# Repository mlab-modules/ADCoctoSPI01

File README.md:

# ADCoctoSPI01 - Octal Input High-Speed ADC Module

The ADCoctoSPI01 is an eight-channel, high-speed analog-to-digital conversion module designed for signal acquisition in imaging and similar high-speed applications. It integrates a Texas Instruments AFE5801 analog front-end (AFE), which combines eight variable-gain amplifiers (VGAs) and eight 12-bit ADCs with a sampling rate up to 65 MSPS. Data output is serialized through an LVDS interface.

This module is ideally used in combination with the [MPPB01 baseboard for Parallella](https://www.mlab.cz/module/MPPB01/), which features a compatible miniSAS connector, allowing for direct integration and high-speed data transfer.

## Features

* **8 differential analog input channels**
* **Integrated AFE5801 from Texas Instruments**
  * 8x VGAs with -5 dB to 31 dB gain range
  * 8x 12-bit ADCs, up to 65 MSPS sampling rate
  * Integrated anti-aliasing filter (7.5 / 10 / 14 MHz selectable)
  * Serial LVDS output
  * SPI control interface
* **MiniSAS (SFF-8087) connector for LVDS data output**
* **Separate SPI interface for configuration and diagnostics**
* **On-board linear regulators for 1.8V and 3.3V supplies**
* **Operating voltage: 3.6 V to 5.4 V**
* **Operating temperature: -20 °C to +40 °C**

## Technical Specifications

| Parameter                       | Value             | Description                          |
| ------------------------------- | ----------------- | ------------------------------------ |
| ADC Resolution                  | 12 bits           | Per channel                          |
| Number of Channels              | 8                 | Differential                         |
| Max Sampling Rate               | 65 MSPS           | Per channel                          |
| Input Voltage Swing             | 2 Vpp             | Differential, max linear input range |
| VGA Gain Range                  | -5 dB to +31 dB   | Step size: 0.125/1 dB                |
| Input Referred Noise            | 5.5 nV/√Hz        | At VGA gain = 31 dB                  |
| Signal-to-Noise Ratio (SNR)     | ~65 dBFS          | Typical at 65 MSPS, -1 dBFS input    |
| Total Harmonic Distortion (THD) | -65 dBFS          | At 5 MHz input, max gain             |
| Signal-to-Noise and Distortion Ratio (SINAD) | ~68 dB            |                                      |
| Antialias Filter Cutoff         | 7.5 / 10 / 14 MHz | Programmable                         |
| Common-Mode Input Voltage (VCM) | 1.6 V             | Recommended bias for AC coupling     |
| Input Capacitance               | 2 pF              | Differential input                   |
| Input Resistance                | 5 kΩ              | To internal bias                     |

## Connectors

* **J1-J4**: Differential analog inputs (IN1P/M to IN8P/M) (SATA connectors)
* **J10A**: MiniSAS connector for serialized LVDS data (D1-D8, FCLK, DCLK)
* **J8**: SPI control interface (SCLK, SDATA, SDOUT, SEN, RESET, SYNC)
* **J11**: Power input (+5V, GND)

## Power Supply

* Requires a single 5V power supply.
* Onboard regulators generate 3.3V and 1.8V for AFE operation.

## AFE5801 Configuration Highlights

* **Gain Control**: SPI-controlled VGA gain, from -5 dB to 31 dB in 0.125 dB or 1 dB steps
* **Clamping and Filtering**: Optional signal clamping and integrated third-order low-pass filter
* **Sampling Clock**: Differential clock input (LVDS/PECL supported)
* **LVDS Output**: Serialized outputs for each channel (D1-D8), frame clock (FCLK), and data clock (DCLK)

## Typical Applications

* Medical ultrasound systems
* Non-destructive testing
* High-speed data acquisition
* Multichannel signal digitization in SDR receivers

## References

* [AFE5801 Datasheet](https://www.ti.com/product/AFE5801)
* Other compatible AFEs: AFE5805, AFE5809 (with differing performance and power specs)

## Notes

* Only the AFE5801 is populated by default; board supports footprint-compatible variants (AFE5803, AFE5804 etc.).
* For optimal performance, ensure proper analog signal termination and impedance matching on all differential inputs.
* Follow ESD precautions during handling.

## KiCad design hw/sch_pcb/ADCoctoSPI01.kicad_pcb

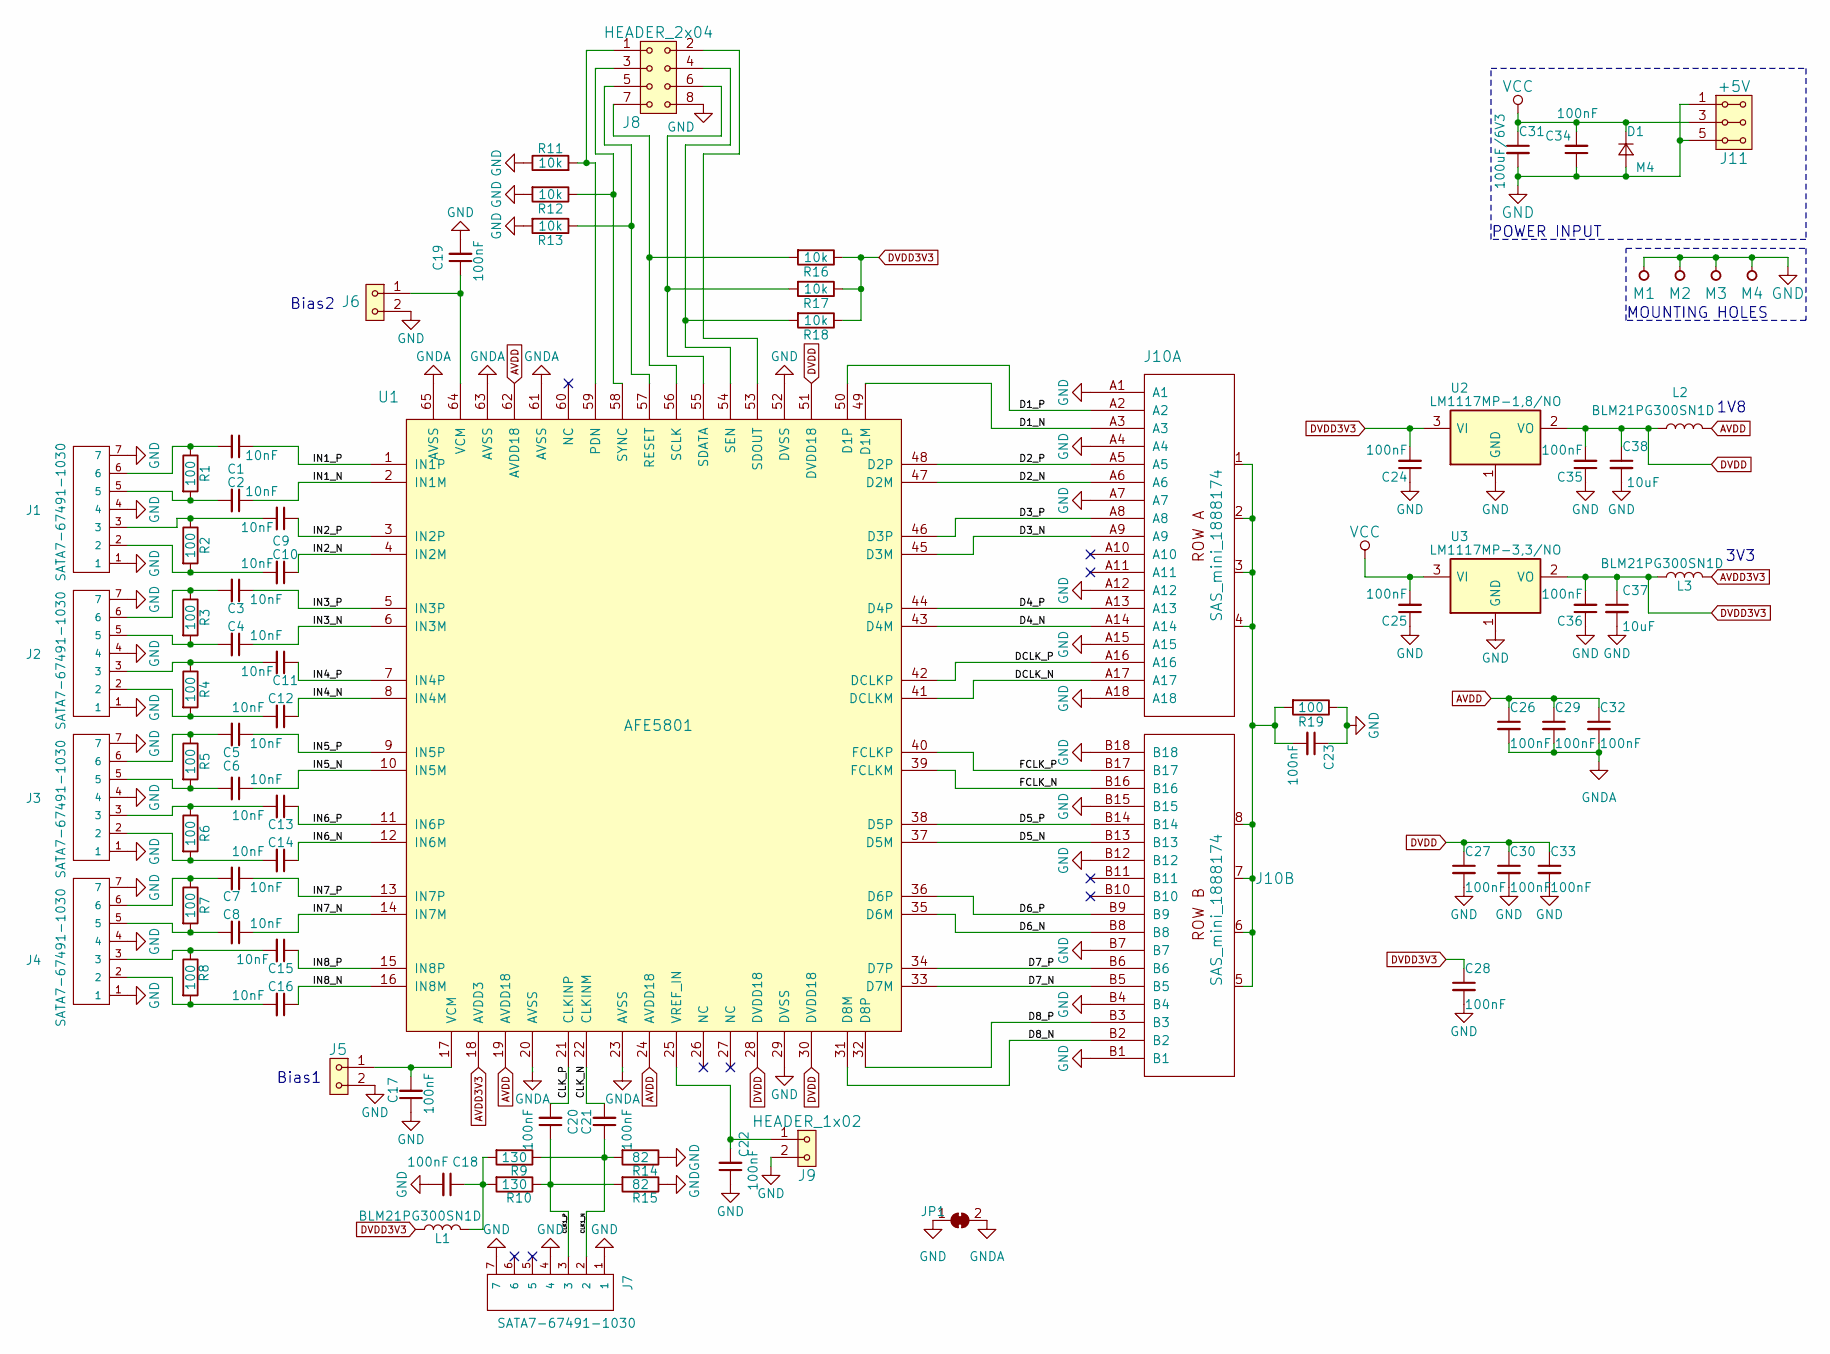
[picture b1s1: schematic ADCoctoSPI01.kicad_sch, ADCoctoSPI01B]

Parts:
C1, C2, C3, C4, C5, C6, C7, C8, C9, C10, C11, C12, C13, C14, C15, C16: 10nF; C_0603_1608Metric
C17, C18, C19, C20, C21, C22, C23, C24, C25, C26, C27, C28, C29, C30, C32, C33, C34, C35, C36: 100nF; C_0603_1608Metric
C31: 100uF/6V3; C_1210_3225Metric_Pad1.33x2.70mm_HandSolder
C37, C38: 10uF; C_0805_2012Metric
D1: M4; D_SMA
J1, J2, J3, J4, J7: SATA7-67491-1030; SATA-7_THT_VERT_2
J5, J6, J9: HEADER_1x02; Straight_1x02
J8: HEADER_2x04; Straight_2x04
J10: SAS_mini_1888174; SAS-mini_TEConnectivity_1888174_Vertical
J11: +5V; Straight_2x03
JP1: SolderJumper_2_Bridged; NetTie-2_SMD_Pad0.5mm
L1, L2, L3: BLM21PG300SN1D; L_0805_2012Metric_Pad1.15x1.40mm_HandSolder
M1, M2, M3, M4: HOLE; MountingHole_3mm
R1, R2, R3, R4, R5, R6, R7, R8, R19: 100; R_0603_1608Metric
R9, R10: 130; R_0603_1608Metric
R11, R12, R13, R16, R17, R18: 10k; R_0603_1608Metric
R14, R15: 82; R_0603_1608Metric
U1: AFE5801; VQFN-64_9.15x9.15mm_EP_7.5x7.5mm
U2: LM1117MP-1,8/NO; SOT-223-3_TabPin2
U3: LM1117MP-3,3/NO; SOT-223-3_TabPin2

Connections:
/CLK1_N: C21.1, J7.2, R9.1, R14.2
/CLK1_P: C20.1, J7.3, R10.1, R15.2
/CLK_N: C21.2, U1.22 (CLKINM)
/CLK_P: C20.2, U1.21 (CLKINP)
/D1_N: J10.A3, U1.49 (D1M)
/D1_P: J10.A2, U1.50 (D1P)
/D2_N: J10.A6, U1.47 (D2M)
/D2_P: J10.A5, U1.48 (D2P)
/D3_N: J10.A9, U1.45 (D3M)
/D3_P: J10.A8, U1.46 (D3P)
/D4_N: J10.A14, U1.43 (D4M)
/D4_P: J10.A13, U1.44 (D4P)
/D5_N: J10.B13, U1.37 (D5M)
/D5_P: J10.B14, U1.38 (D5P)
/D6_N: J10.B8, U1.35 (D6M)
/D6_P: J10.B9, U1.36 (D6P)
/D7_N: J10.B5, U1.33 (D7M)
/D7_P: J10.B6, U1.34 (D7P)
/D8_N: J10.B2, U1.31 (D8M)
/D8_P: J10.B3, U1.32 (D8P)
/DCLK_N: J10.A17, U1.41 (DCLKM)
/DCLK_P: J10.A16, U1.42 (DCLKP)
/FCLK_N: J10.B16, U1.39 (FCLKM)
/FCLK_P: J10.B17, U1.40 (FCLKP)
/IN1_N: C2.1, U1.2 (IN1M)
/IN1_P: C1.1, U1.1 (IN1P)
/IN2_N: C10.1, U1.4 (IN2M)
/IN2_P: C9.1, U1.3 (IN2P)
/IN3_N: C4.1, U1.6 (IN3M)
/IN3_P: C3.1, U1.5 (IN3P)
/IN4_N: C12.1, U1.8 (IN4M)
/IN4_P: C11.1, U1.7 (IN4P)
/IN5_N: C6.1, U1.10 (IN5M)
/IN5_P: C5.1, U1.9 (IN5P)
/IN6_N: C14.1, U1.12 (IN6M)
/IN6_P: C13.1, U1.11 (IN6P)
/IN7_N: C8.1, U1.14 (IN7M)
/IN7_P: C7.1, U1.13 (IN7P)
/IN8_N: C16.1, U1.16 (IN8M)
/IN8_P: C15.1, U1.15 (IN8P)
AVDD: C26.1, C29.1, C32.1, L2.2, U1.19 (AVDD18), U1.24 (AVDD18), U1.62 (AVDD18)
AVDD3V3: L3.2, U1.18 (AVDD3)
DVDD: C27.1, C30.1, C33.1, C35.2, C38.1, L2.1, U1.28 (DVDD18), U1.30 (DVDD18), U1.51 (DVDD18), U2.2 (VO)
DVDD3V3: C24.2, C28.1, C36.2, C37.1, L1.1, L3.1, R16.1, R17.1, R18.1, U2.3 (VI), U3.2 (VO)
GND: C17.1, C18.2, C19.2, C22.1, C23.1, C24.1, C25.1, C27.2, C28.2, C30.2, C31.2, C33.2, C34.1, C35.1, C36.1, C37.2, C38.2, D1.2 (A), J1.1, J1.4, J1.7, J2.1, J2.4, J2.7, J3.1, J3.4, J3.7, J4.1, J4.4, J4.7, J5.2, J6.2, J7.1, J7.4, J7.7, J8.8, J9.2, J10.A1, J10.A4, J10.A7, J10.A12, J10.A15, J10.A18, J10.B1, J10.B4, J10.B7, J10.B12, J10.B15, J10.B18, J11.1, J11.2, J11.5, J11.6, JP1.1 (A), M1.1, M2.1, M3.1, M4.1, R11.1, R12.2, R13.2, R14.1, R15.1, R19.1, U1.29 (DVSS), U1.52 (DVSS), U2.1 (GND), U3.1 (GND)
GNDA: C26.2, C29.2, C32.2, JP1.2 (B), U1.20 (AVSS), U1.23 (AVSS), U1.61 (AVSS), U1.63 (AVSS), U1.65 (AVSS)
unnamed: C1.2, J1.6, R1.1
unnamed: C2.2, J1.5, R1.2
unnamed: C3.2, J2.6, R3.1
unnamed: C4.2, J2.5, R3.2
unnamed: C5.2, J3.6, R5.1
unnamed: C6.2, J3.5, R5.2
unnamed: C7.2, J4.6, R7.1
unnamed: C8.2, J4.5, R7.2
unnamed: C9.2, J1.3, R2.1
unnamed: C10.2, J1.2, R2.2
unnamed: C11.2, J2.3, R4.1
unnamed: C12.2, J2.2, R4.2
unnamed: C13.2, J3.3, R6.1
unnamed: C14.2, J3.2, R6.2
unnamed: C15.2, J4.3, R8.1
unnamed: C16.2, J4.2, R8.2
unnamed: C17.2, J5.1, U1.17 (VCM)
unnamed: C18.1, L1.2, R9.2, R10.2
unnamed: C19.1, J6.1, U1.64 (VCM)
unnamed: C23.2, J10.1, J10.2, J10.3, J10.4, J10.5, J10.6, J10.7, J10.8, R19.2
unnamed: J8.1, R11.2, U1.59 (PDN)
unnamed: J8.5, R13.1, U1.57 (RESET)
unnamed: J8.7, R16.2, U1.56 (SCLK)
unnamed: J8.6, R17.2, U1.55 (SDATA)
unnamed: J8.2, U1.53 (SDOUT)
unnamed: J8.4, R18.2, U1.54 (SEN)
unnamed: J8.3, R12.1, U1.58 (SYNC)
unnamed: C22.2, J9.1, U1.25 (VREF_IN)
VCC: C25.2, C31.1, C34.2, D1.1 (K), J11.3, J11.4, U3.3 (VI)

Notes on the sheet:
Bias1
Bias2
POWER INPUT
MOUNTING HOLES
1V8
3V3

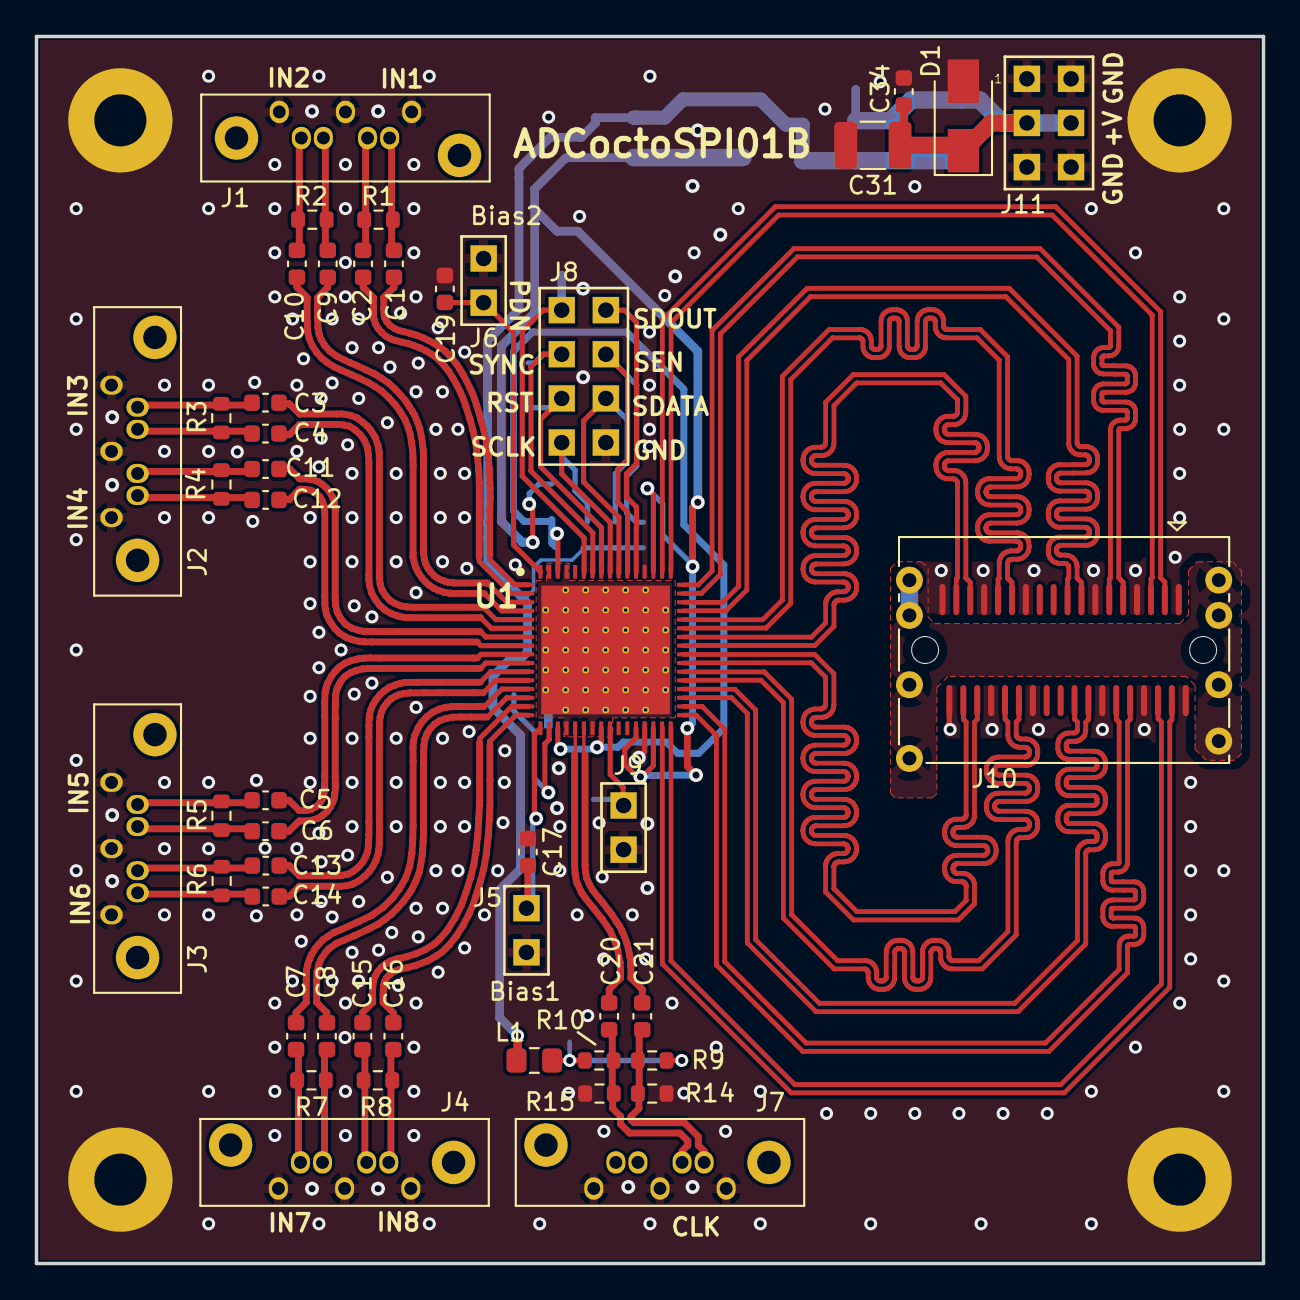
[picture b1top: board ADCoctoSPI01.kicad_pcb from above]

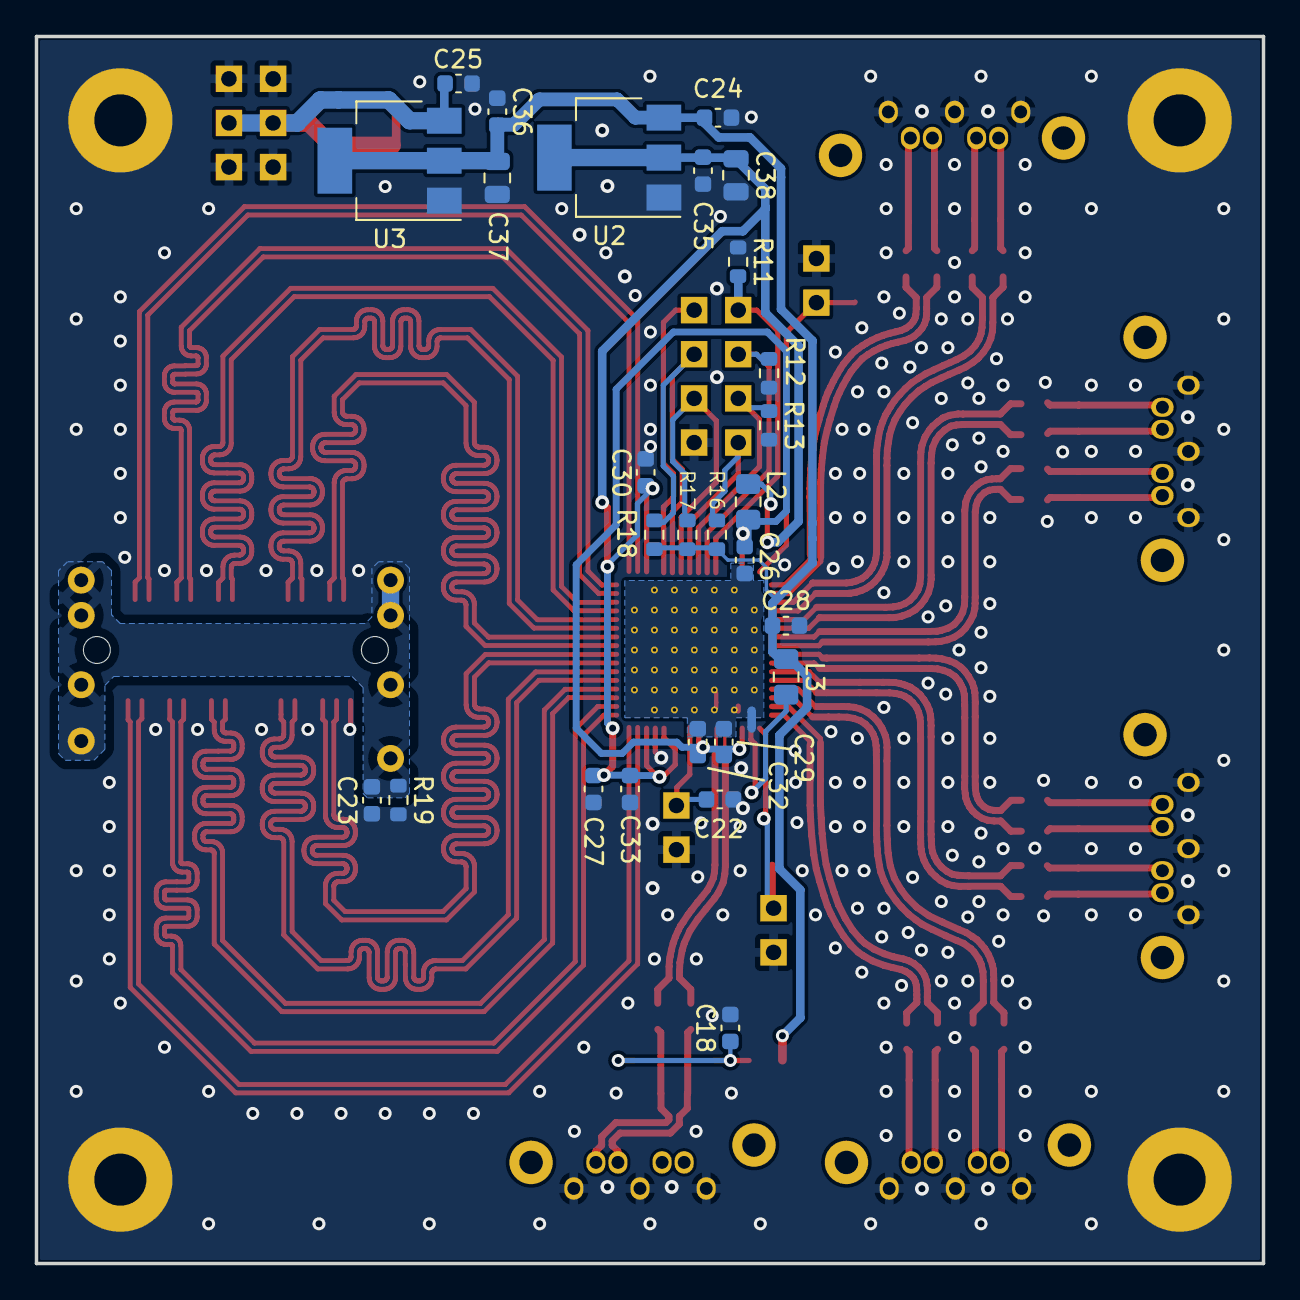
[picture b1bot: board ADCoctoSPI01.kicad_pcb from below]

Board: 2 copper layers, 70.6 x 70.6 mm, 80 parts (28 on the bottom side), 75 nets.

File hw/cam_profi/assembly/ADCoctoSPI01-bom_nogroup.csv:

Component,Description,Part,References,Value,Footprint,Quantity Per PCB,Datasheet,ust_id
1,,C_Small-device,C1C2C3C4C5C6C7C8C9C10C11C12C13C14C15C16,10nF,C_0603_1608Metric,16,,5c70984812875079b91f8bef
2,,C_Small-device,C17C18C19C20C21C22C23C24C25C26C27C28C29C30C32C33C34C35C36,100nF,C_0603_1608Metric,19,,5c70984812875079b91f8bf2
3,,C_Small-device,C37C38,10uF,C_0805_2012Metric,2,,5c70984812875079b91f8bbd
4,,C_Small-device,C31,100uF/6V3,C_1210_3225Metric_Pad1.33x2.70mm_HandSolder,1,https://www.tme.eu/sk/katalog/#search=100uf+1210&s_field=acc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,5c70984812875079b91f8bbb
5,,D_Small-device,D1,M4,D_SMA,1,,5c70984512875079b91f88ac
6,,HEADER_2x03_PARALLEL-MLAB_HEADER,J11,+5V,Straight_2x03,1,,
7,,HEADER_1x02-MLAB_HEADER,J5J6J9,HEADER_1x02,Straight_1x02,3,,
8,,HEADER_2x04-MLAB_HEADER,J8,HEADER_2x04,Straight_2x04,1,,
9,,SAS_mini_1888174-MLAB_CONNECTORS,J10,SAS_mini_1888174,SAS-mini_TEConnectivity_1888174_Vertical,1,,624ede60592c2d62176d5a96
10,,SATA7-67491-1030-MLAB_CONNECTORS,J1J2J3J4J7,SATA7-67491-1030,SATA-7_THT_VERT_2,5,,5c70984712875079b91f8a7b
11,,L-device,L1L2L3,BLM21PG300SN1D,L_0805_2012Metric_Pad1.15x1.40mm_HandSolder,3,,5c70984412875079b91f87fd
12,,R-device,R14R15,82,R_0603_1608Metric,2,,5c70984512875079b91f8955
13,,R-device,R1R2R3R4R5R6R7R8R19,100,R_0603_1608Metric,9,,5c70984512875079b91f8956
14,,R-device,R9R10,130,R_0603_1608Metric,2,,5cd08b17128750448e4542b1
15,,R-device,R11R12R13R16R17R18,10k,R_0603_1608Metric,6,,5c70984512875079b91f8962
16,,AFE5801-DENGS_lib,U1,AFE5801,VQFN-64_9.15x9.15mm_EP_7.5x7.5mm,1,https://www.ti.com/lit/ds/symlink/afe5801.pdf,624edf21592c2d62176d5abc
17,,LD1117S18TR-RESCUE-ADCoctoSPI01A,U2,"LM1117MP-1,8/NO",SOT-223-3_TabPin2,1,,5c70984712875079b91f8af6
18,,LD1117S33TR-RESCUE-ADCoctoSPI01A,U3,"LM1117MP-3,3/NO",SOT-223-3_TabPin2,1,,5c70984712875079b91f8af9

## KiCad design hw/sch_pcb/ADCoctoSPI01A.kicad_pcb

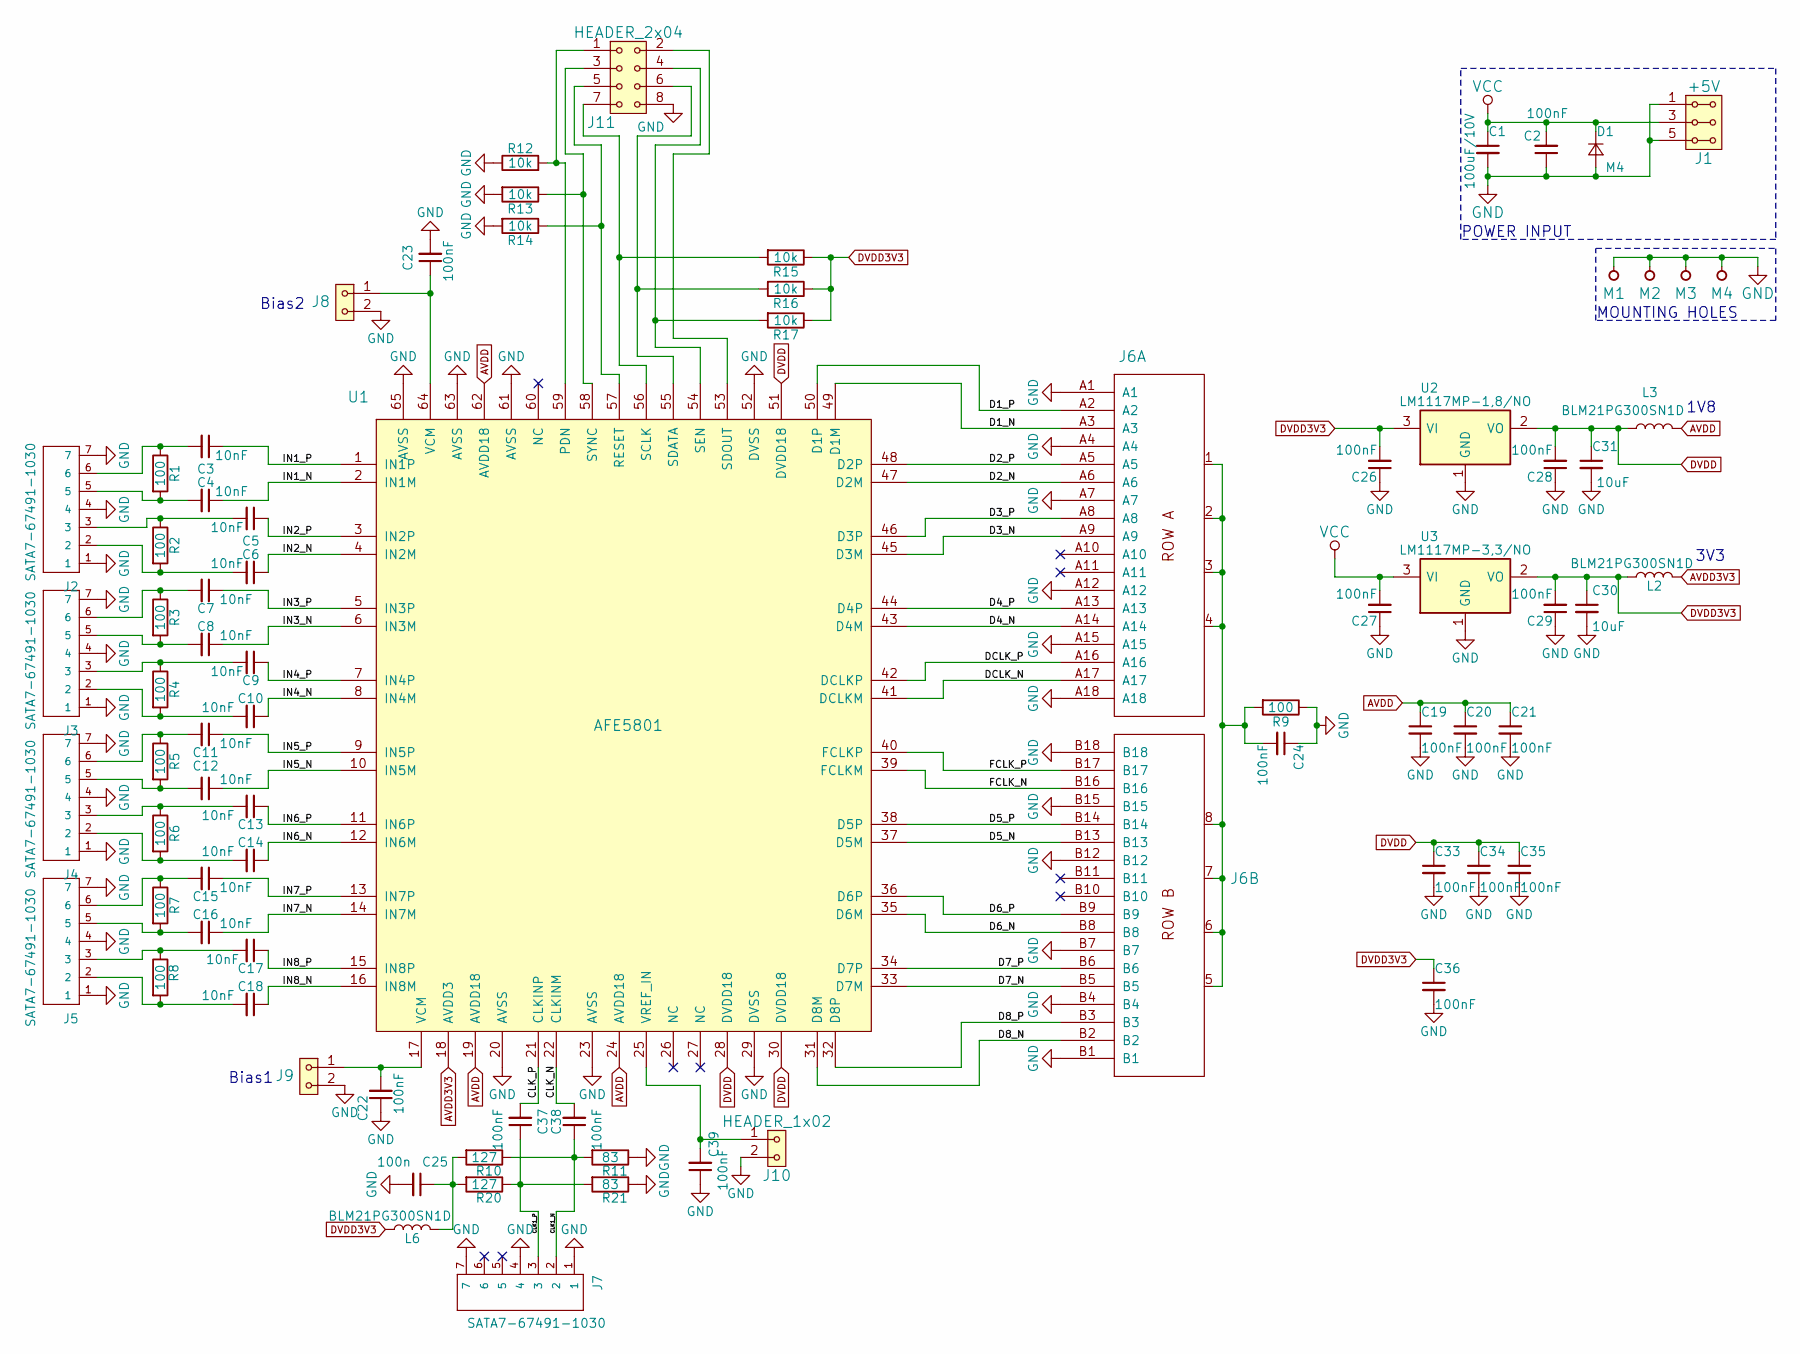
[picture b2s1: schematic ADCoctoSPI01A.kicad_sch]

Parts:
C1: 100uF/10V; C_1210_HandSoldering
C2, C19, C20, C21, C22, C23, C24, C26, C27, C28, C29, C33, C34, C35, C36, C37, C38, C39: 100nF; SMD-0603_narrow
C3, C4, C5, C6, C7, C8, C9, C10, C11, C12, C13, C14, C15, C16, C17, C18: 10nF; SMD-0603_narrow
C25: 100n; SMD-0603_narrow
C30, C31: 10uF; SMD-0805
D1: M4; D_SMA
J1: +5V; Straight_2x03
J2, J3, J4, J5, J7: SATA7-67491-1030; SATA-7_THT_VERT_2
J6: (no value)
J8, J9, J10: HEADER_1x02; Straight_1x02
J11: HEADER_2x04; Straight_2x04
L2, L3, L6: BLM21PG300SN1D; SMD-0805
M1, M2, M3, M4: HOLE; MountingHole_3mm
R1, R2, R3, R4, R5, R6, R7, R8, R9: 100; SMD-0603
R10, R20: 127; SMD-0603
R11, R21: 83; SMD-0603
R12, R13, R14, R15, R16, R17: 10k; SMD-0603
U1: AFE5801; QFN-64-1EP_9x9mm_Pitch0.5mm
U2: LM1117MP-1,8/NO; SOT-223-3_TabPin2
U3: LM1117MP-3,3/NO; SOT-223-3_TabPin2

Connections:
/CLK1_N: C38.1, J7.2, R10.1, R11.2
/CLK1_P: C37.1, J7.3, R20.1, R21.2
/CLK_N: C38.2, U1.22 (CLKINM)
/CLK_P: C37.2, U1.21 (CLKINP)
/D1_N: J6.A3, U1.49 (D1M)
/D1_P: J6.A2, U1.50 (D1P)
/D2_N: J6.A6, U1.47 (D2M)
/D2_P: J6.A5, U1.48 (D2P)
/D3_N: J6.A9, U1.45 (D3M)
/D3_P: J6.A8, U1.46 (D3P)
/D4_N: J6.A14, U1.43 (D4M)
/D4_P: J6.A13, U1.44 (D4P)
/D5_N: J6.B13, U1.37 (D5M)
/D5_P: J6.B14, U1.38 (D5P)
/D6_N: J6.B8, U1.35 (D6M)
/D6_P: J6.B9, U1.36 (D6P)
/D7_N: J6.B5, U1.33 (D7M)
/D7_P: J6.B6, U1.34 (D7P)
/D8_N: J6.B2, U1.31 (D8M)
/D8_P: J6.B3, U1.32 (D8P)
/DCLK_N: J6.A17, U1.41 (DCLKM)
/DCLK_P: J6.A16, U1.42 (DCLKP)
/FCLK_N: J6.B16, U1.39 (FCLKM)
/FCLK_P: J6.B17, U1.40 (FCLKP)
/IN1_N: C4.1, U1.2 (IN1M)
/IN1_P: C3.1, U1.1 (IN1P)
/IN2_N: C6.1, U1.4 (IN2M)
/IN2_P: C5.1, U1.3 (IN2P)
/IN3_N: C8.1, U1.6 (IN3M)
/IN3_P: C7.1, U1.5 (IN3P)
/IN4_N: C10.1, U1.8 (IN4M)
/IN4_P: C9.1, U1.7 (IN4P)
/IN5_N: C12.1, U1.10 (IN5M)
/IN5_P: C11.1, U1.9 (IN5P)
/IN6_N: C14.1, U1.12 (IN6M)
/IN6_P: C13.1, U1.11 (IN6P)
/IN7_N: C16.1, U1.14 (IN7M)
/IN7_P: C15.1, U1.13 (IN7P)
/IN8_N: C18.1, U1.16 (IN8M)
/IN8_P: C17.1, U1.15 (IN8P)
AVDD: C19.1, C20.1, C21.1, L3.2, U1.19 (AVDD18), U1.24 (AVDD18), U1.62 (AVDD18)
AVDD3V3: L2.2, U1.18 (AVDD3)
DVDD: C28.2, C31.1, C33.1, C34.1, C35.1, L3.1, U1.28 (DVDD18), U1.30 (DVDD18), U1.51 (DVDD18), U2.2 (VO)
DVDD3V3: C26.2, C29.2, C30.1, C36.1, L2.1, L6.1, R15.1, R16.1, R17.1, U2.3 (VI), U3.2 (VO)
GND: C1.2, C2.1, C19.2, C20.2, C21.2, C22.1, C23.2, C24.1, C25.2, C26.1, C27.1, C28.1, C29.1, C30.2, C31.2, C33.2, C34.2, C35.2, C36.2, C39.1, D1.2 (A), J1.1, J1.2, J1.5, J1.6, J2.1, J2.4, J2.7, J3.1, J3.4, J3.7, J4.1, J4.4, J4.7, J5.1, J5.4, J5.7, J6.A1, J6.A4, J6.A7, J6.A12, J6.A15, J6.A18, J6.B1, J6.B4, J6.B7, J6.B12, J6.B15, J6.B18, J7.1, J7.4, J7.7, J8.2, J9.2, J10.2, J11.8, M1.1, M2.1, M3.1, M4.1, R9.1, R11.1, R12.1, R13.2, R14.2, R21.1, U1.20 (AVSS), U1.23 (AVSS), U1.29 (DVSS), U1.52 (DVSS), U1.61 (AVSS), U1.63 (AVSS), U1.65 (AVSS), U2.1 (GND), U3.1 (GND)
unnamed: C3.2, J2.6, R1.1
unnamed: C4.2, J2.5, R1.2
unnamed: C5.2, J2.3, R2.1
unnamed: C6.2, J2.2, R2.2
unnamed: C7.2, J3.6, R3.1
unnamed: C8.2, J3.5, R3.2
unnamed: C9.2, J3.3, R4.1
unnamed: C10.2, J3.2, R4.2
unnamed: C11.2, J4.6, R5.1
unnamed: C12.2, J4.5, R5.2
unnamed: C13.2, J4.3, R6.1
unnamed: C14.2, J4.2, R6.2
unnamed: C15.2, J5.6, R7.1
unnamed: C16.2, J5.5, R7.2
unnamed: C17.2, J5.3, R8.1
unnamed: C18.2, J5.2, R8.2
unnamed: C22.2, J9.1, U1.17 (VCM)
unnamed: C23.1, J8.1, U1.64 (VCM)
unnamed: C24.2, J6.1, J6.2, J6.3, J6.4, J6.5, J6.6, J6.7, J6.8, R9.2
unnamed: C25.1, L6.2, R10.2, R20.2
unnamed: C39.2, J10.1, U1.25 (VREF_IN)
unnamed: J11.1, R12.2, U1.59 (PDN)
unnamed: J11.2, U1.53 (SDOUT)
unnamed: J11.3, R13.1, U1.58 (SYNC)
unnamed: J11.4, R17.2, U1.54 (SEN)
unnamed: J11.5, R14.1, U1.57 (RESET)
unnamed: J11.6, R16.2, U1.55 (SDATA)
unnamed: J11.7, R15.2, U1.56 (SCLK)
VCC: C1.1, C2.2, C27.2, D1.1 (K), J1.3, J1.4, U3.3 (VI)

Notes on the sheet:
Bias1
Bias2
POWER INPUT
MOUNTING HOLES
1V8
3V3

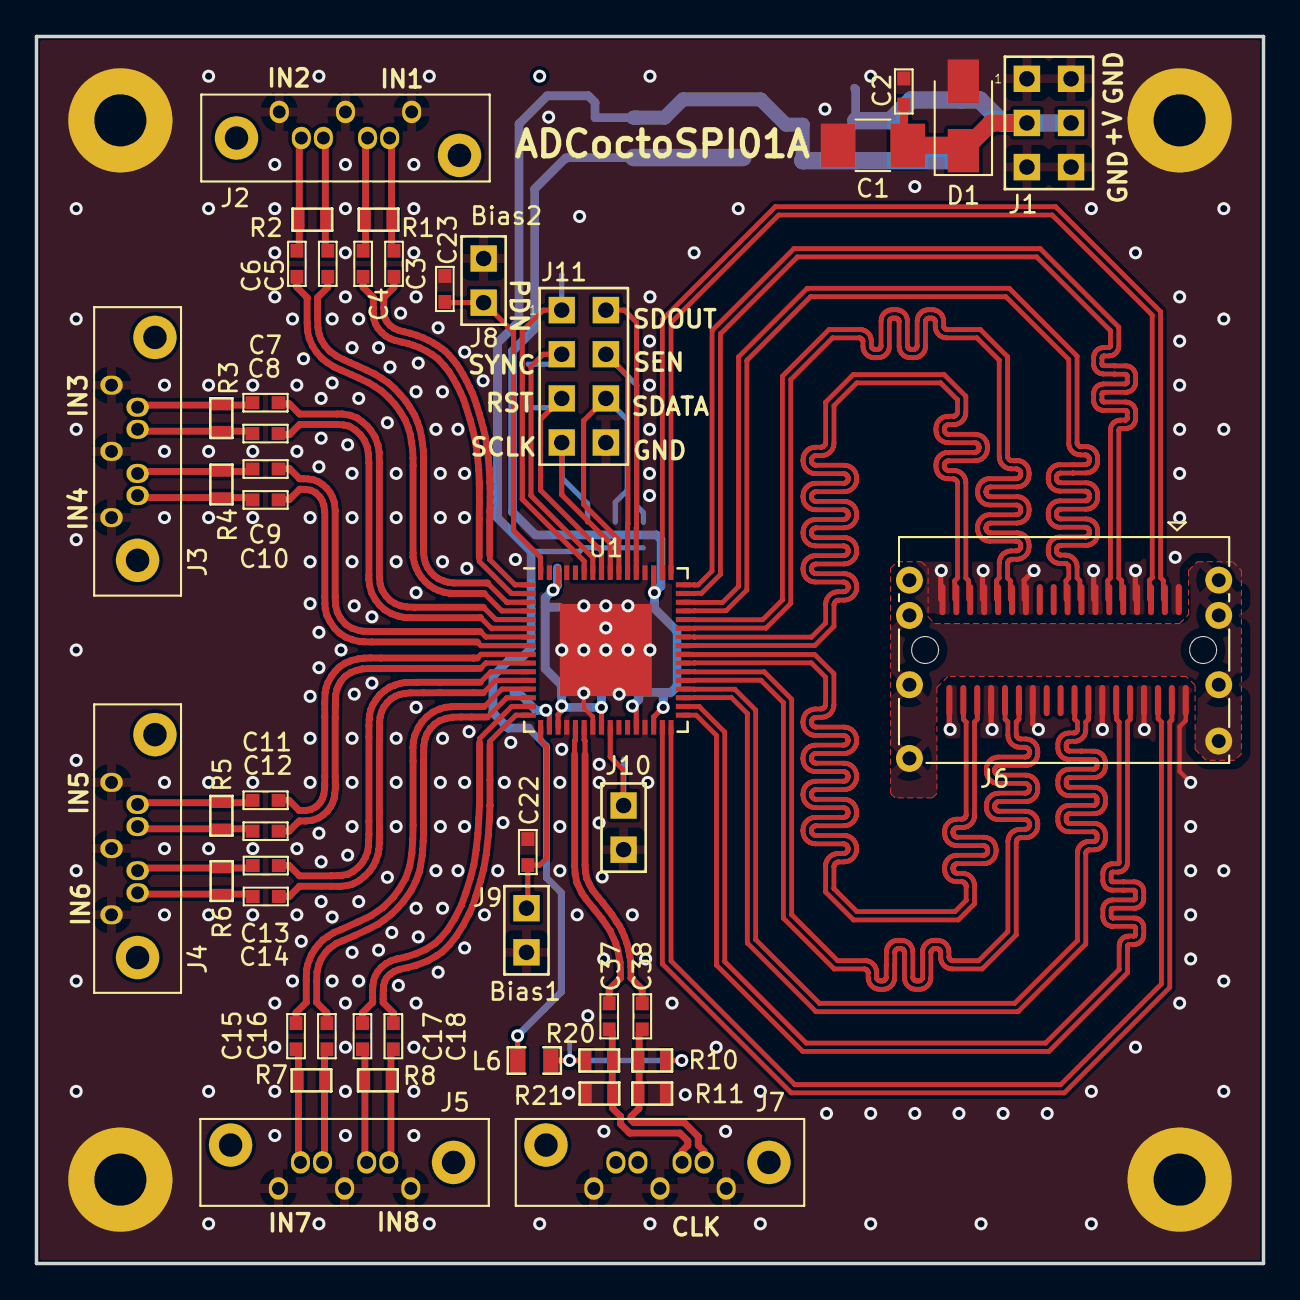
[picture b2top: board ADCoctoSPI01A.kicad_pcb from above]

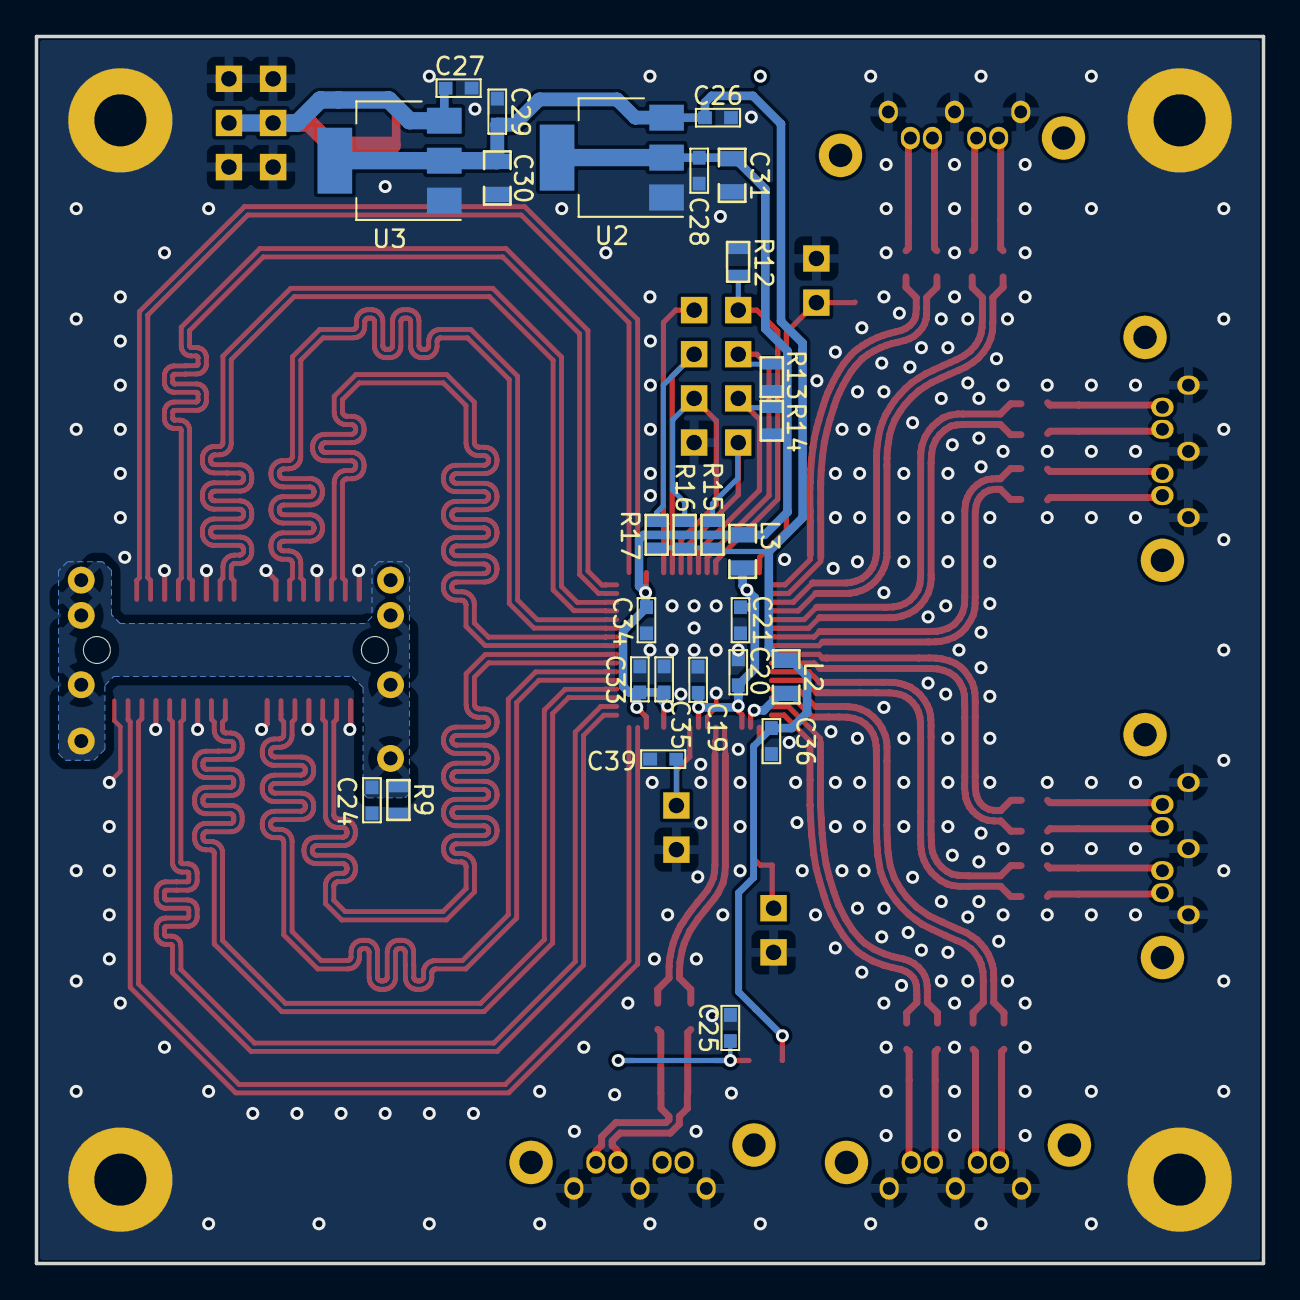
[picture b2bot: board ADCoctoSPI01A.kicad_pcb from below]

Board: 2 copper layers, 70.6 x 70.6 mm, 79 parts (27 on the bottom side), 74 nets.

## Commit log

2020-06-15 Adding new ADC design.
2021-04-14 Add workflow file.
2021-04-14 schematic title block update.
2022-02-17 Repository cleanup Update of KiCAD project version to 6.0.1.
2022-03-11 Add a link to schematics.
2022-03-24 Update footprints.
2022-03-25 Update mini SAS connector footprint to up to date footprint from KiCAD library.
2022-03-25 Repair footprint #2.
2022-03-26 Update miniSAS connector footprint.
2022-04-05 Prejmenovani Kicad projektu
2022-04-05 Edit PCB
2022-04-05 Remove KiCAD backups and attempt to fix that by introducing a gitignore file.
2022-04-06 Edit footprints + 3d models
2022-04-06 Aktualizace doc/assets
2022-04-06 new workflows/kicad_outputs.yml
2022-04-06 Update actions products
2022-04-06 aktualizace submodulu
2022-04-06 assets
2022-04-06 clean repo
2022-04-06 automated commit; add github actions
2022-04-06 Edit footprint AFE5801
2022-04-07 Edit bom
2022-05-17 uprava layoutu
2022-05-18 rozdeleni VSSA a VSSD
2022-05-18 uprava AGND
2022-05-18 doroutovani cest
2022-05-19 Improve GND layout.
2022-05-19 uprava routovani, premisteni soucastek, AVDD k hodinam
2022-05-19 drobne upravy routovani
2022-05-25 Příprava podkladů pro osazení
2022-06-28 cleanup traces in schematics.
2022-08-21 Cleanup schematics.
2022-08-21 remove duplicite datasheet.
2023-09-17 Delete ADCoctoSPI01A.json
    Delete json without useful data.
2025-10-24 Update to KiCADv9.
2025-10-24 Update workflow files
2025-10-24 Update metadata files
2025-10-24 Update readme description.
2025-10-24 Update README.md
    Add calculated SINAD value.
